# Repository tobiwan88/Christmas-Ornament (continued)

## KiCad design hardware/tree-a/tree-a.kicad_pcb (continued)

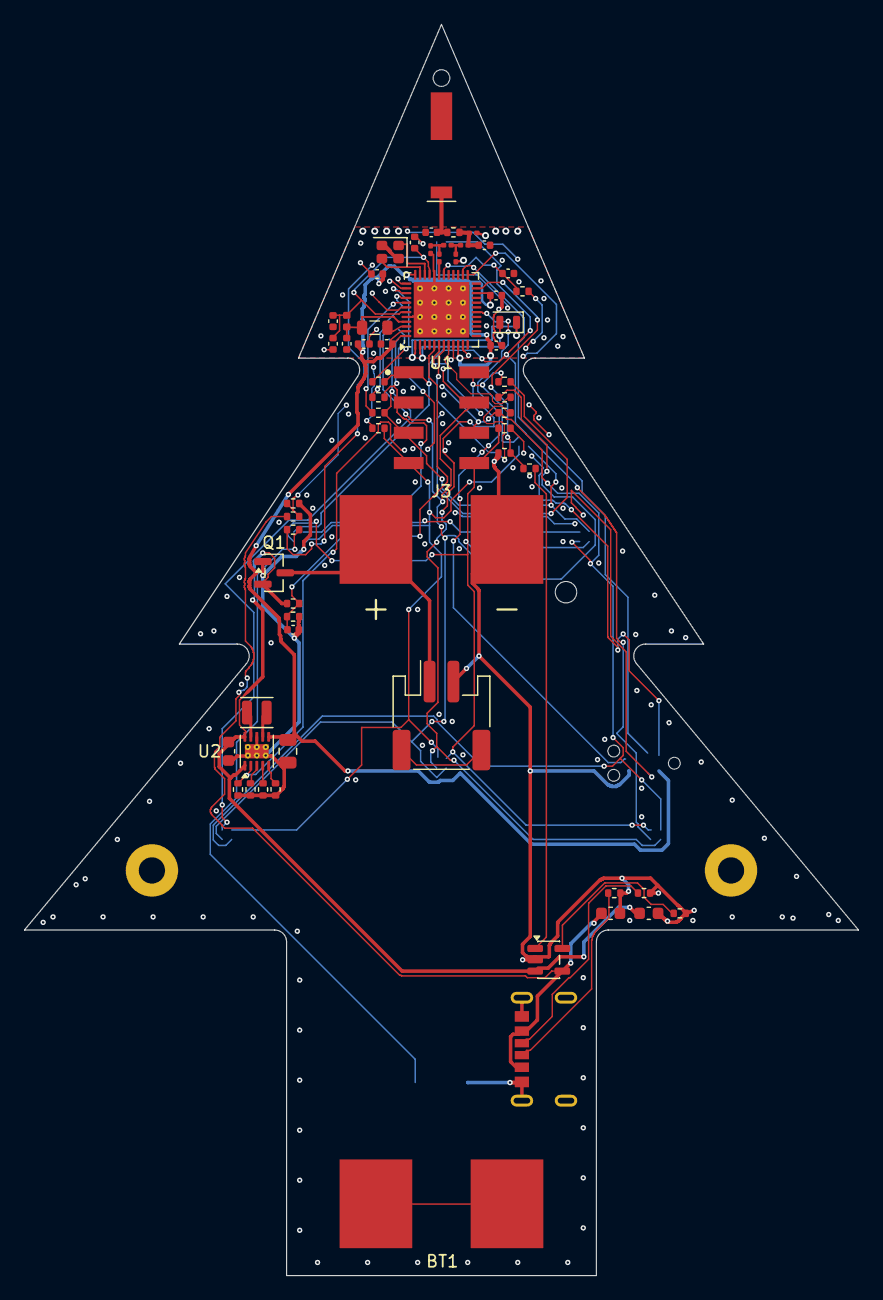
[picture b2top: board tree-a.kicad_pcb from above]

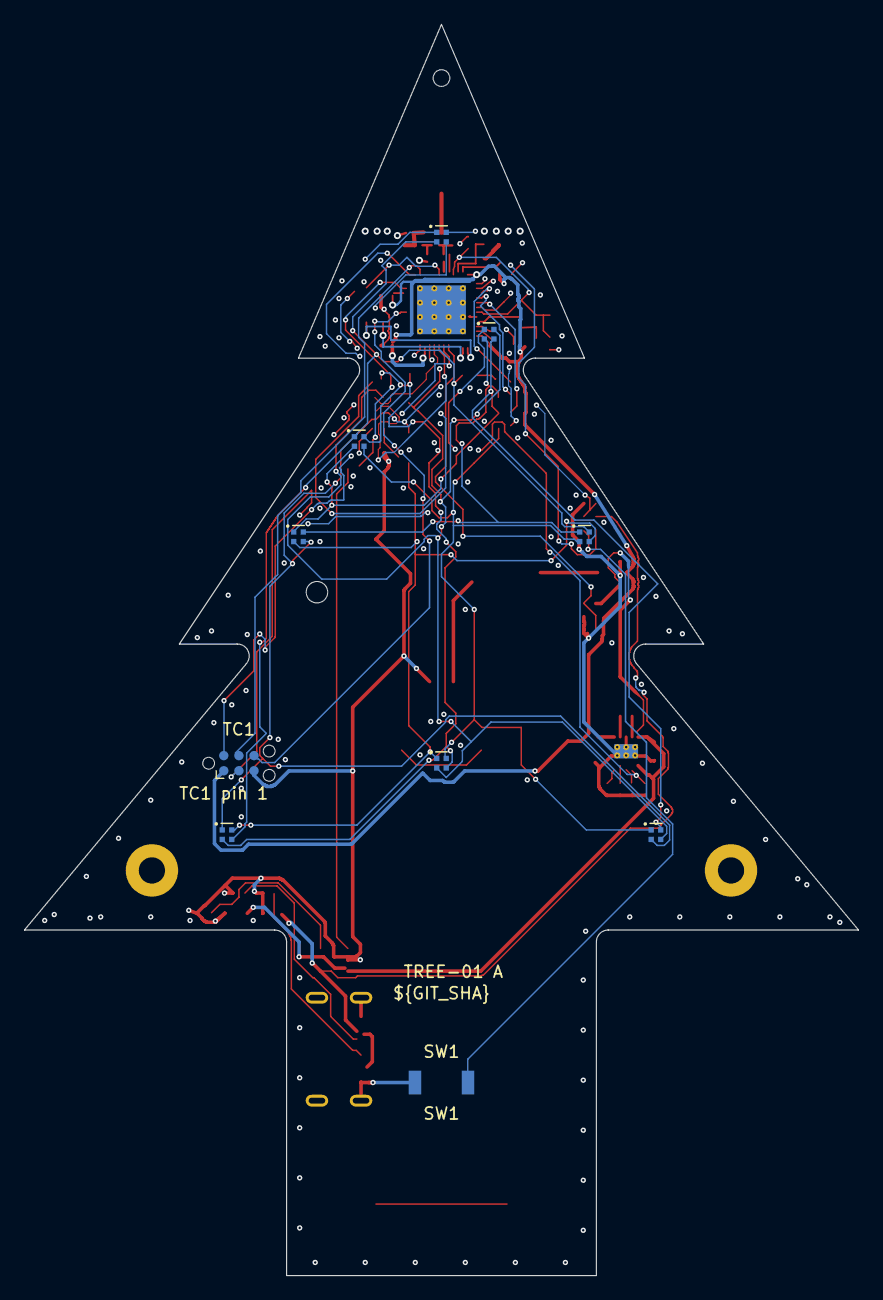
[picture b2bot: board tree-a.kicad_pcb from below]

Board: 4 copper layers, 70.0 x 105.0 mm, 75 parts (10 on the bottom side), 55 nets.

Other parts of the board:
H1: H_HANG; Hole_NPTH_1.4mm

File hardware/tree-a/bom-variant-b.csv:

Comment,Designator,Footprint,Quantity,LCSC Part #,Class,Status,Function / notes
2450AT42A100E (5x2mm),ANT1,ANT_Johanson_2450AT42A100E,1,C2917719,Extended,"datasheet card, stock 2026-11-23 (PARTS-REVIEW)","chip antenna (D12), feed pad 1 at the mark end (UNVERIFIED)"
2.2uF 6.3V X5R (0402),"C1,C2",C_0402_1005Metric,2,C12530,Basic,"datasheet card, stock 2026-11-23 (PARTS-REVIEW)",DECD (ref C1); DECA/DECRF (ref C2)
10uF 6.3V X5R (0402),C3,C_0402_1005Metric,1,C15525,Basic,"JLC listing only (jlcparts 2026-11-24, Basic, Samsung CL05A106MQ5NUNC): no card, DC-bias derating UNVERIFIED","VDD bulk at pins 47/48 (ref C3; 0402 for the gate-4 fan-out, alternate C19702 0603)"
100nF 50V X7R (0402),"C4,C7,C8,C10,C14",C_0402_1005Metric,5,C1525,Basic,"datasheet card, stock 2026-11-23 (PARTS-REVIEW)",VDD pin 36; VDD pin 10; VDD pin 22; VDD 47/48; VBAT_SENSE filter (DS-B2)
2.2nF 50V X7R (0402),C5,C_0402_1005Metric,1,C1531,Preferred,"datasheet card, stock 2026-11-23 (PARTS-REVIEW)",DECRF (ref C5)
1.5pF C0G +-0.05pF (0201),C6,C_0201_0603Metric,1,C435397,Extended,"datasheet card, stock 2026-11-23 (PARTS-REVIEW)","RF shunt, ground only via VSS_PA"
2.0pF C0G +-0.05pF (0201),C9,C_0201_0603Metric,1,C668326,Extended,"datasheet card, stock 2026-11-23 (PARTS-REVIEW)","RF shunt, GND via at the pad (KNOWN deviation: Nordic says bottom layer only)"
0.3pF C0G (0201),C11,C_0201_0603Metric,1,C161289,Extended,"datasheet card, stock 2026-11-23 (PARTS-REVIEW)",RF shunt at the 50 ohm node
10nF 50V X7R (0402),C12,C_0402_1005Metric,1,C15195,Basic,"datasheet card, stock 2026-11-23 (PARTS-REVIEW)",DECA/DECRF (ref C12)
3.9pF C0G (0402),C13,C_0402_1005Metric,1,C313081,Extended,"datasheet card, stock 2026-11-23 (PARTS-REVIEW)",nRESET filter (ref C13)
10uF 10V X5R (0603),C20,C_0603_1608Metric,1,C19702,Basic,"datasheet card, stock 2026-11-23 (PARTS-REVIEW)",TPS63900 Cin
22uF 25V X5R (0805),C21,C_0805_2012Metric,1,C45783,Basic,"datasheet card, stock 2026-11-23 (PARTS-REVIEW)",TPS63900 Cout
4.7uF 16V X5R (0603),"C30,C31",C_0603_1608Metric,2,C19666,Basic,"datasheet card, stock 2026-11-23 (PARTS-REVIEW)","charger Cin (variant B); charger Cout on VIN (variant B, D21)"
XL-1010RGB-YG (1010),"D9,D10,D11,D12,D13,D14,D15,D16",LED_XL-1010RGB-YG,8,C965834,Extended,"datasheet card, stock 2026-11-23 (PARTS-REVIEW)","RGB LED, outer face (B.Cu)"
120R/0.2A GZ1005D121TF (0402),FB1,L_0402_1005Metric,1,C38480,Extended,"datasheet card, stock 2026-11-23 (PARTS-REVIEW)",DECD to DECA/DECRF (ref FB1)
HC-TYPE-C-6P-01A (SMD),J1,USB_C_HCTL_HC-TYPE-C-6P-01A,1,C2894893,Extended,"datasheet card, stock 2026-11-23 (PARTS-REVIEW)",USB-C power input (variant B)
S2B-PH-SM4-TB (SMD PH),J2,JST_PH_S2B-PH-SM4-TB_1x02-1MP_P2.00mm_Horizontal,1,C295747,Extended,"datasheet card, stock 2026-11-23 (PARTS-REVIEW)",Li-ion pouch (variant B); pin 1 = cell + (UNVERIFIED)
HC-PM254-8.5H-2x4PS (SMD 2x4 2.54),J3,PinSocket_2x04_SMD_HC-PM254-8.5H,1,C22373945,Extended,"datasheet card, stock 2026-11-23 (PARTS-REVIEW)",female header to board B (D3)
4.7uH MPL2012S4R7MHT (0805),L1,L_0805_2012Metric,1,C63166,Extended,"datasheet card, stock 2026-11-23 (PARTS-REVIEW)",nRF DC/DC DCC-DECD (ref L1)
2.2uH SWPA252012S2R2MT (1008),L2,L_Sunlord_SWPA252012S,1,C23894,Extended,"datasheet card, stock 2026-11-23 (PARTS-REVIEW)","TPS63900 inductor, Isat 1.85 A"
2.7nH LQP03HQ2N7B02D (0201),L3,L_0201_0603Metric,1,C7216765,Extended,"datasheet card, stock 2026-11-23 (PARTS-REVIEW)",RF series (ref L2)
3.5nH LQP03HQ3N5B02D (0201),"L4,L5",L_0201_0603Metric,2,C3911055,Extended,"datasheet card, stock 2026-11-23 (PARTS-REVIEW)",RF series (ref L3); RF series (ref L4)
SI2301CDS-T1-GE3 (SOT-23),Q1,SOT-23,1,C10487,Basic,"datasheet card, stock 2026-11-23 (PARTS-REVIEW)","reverse-polarity P-FET, drain to cell + (D7)"
22R 1% (0402),"R1,R2,R3,R4,R5,R6,R7,R8",R_0402_1005Metric,8,C25092,Basic,"datasheet card, stock 2026-11-23 (PARTS-REVIEW)",line resistor LED_L1 (D13); line resistor LED_L2 (D13); line resistor LED_L3 (D13); line resistor LED_L4 (D13); line resistor LED_L5 (D13); line resistor LED_L6 (D13); line resistor LED_L7 (D13); line resistor LED_L8 (D13)
1k 1% (0402),"R9,R10",R_0402_1005Metric,2,C11702,Basic,"datasheet card, stock 2026-11-23 (PARTS-REVIEW)","nRESET series (ref R1); BTN_SW1 series, ESD current limit (D21, DS-C5)"
511R 1% 100ppm (0402),R20,R_0402_1005Metric,1,C25124,Extended,"datasheet card, stock 2026-11-23 (PARTS-REVIEW)",RCFG1: VO(2) 3.5 V (Table 7-2)
10.5k 1% 100ppm (0402),R21,R_0402_1005Metric,1,C25850,Extended,"datasheet card, stock 2026-11-23 (PARTS-REVIEW)",RCFG2: 100 mA input limit (Table 7-2)
13.3k 1% 100ppm (0402),R22,R_0402_1005Metric,1,C122547,Extended,"datasheet card, stock 2026-11-23 (PARTS-REVIEW)",RCFG3: VO(1) 3.0 V (Table 7-3)
1M 1% (0402),R23,R_0402_1005Metric,1,C26083,Basic,"datasheet card, stock 2026-11-23 (PARTS-REVIEW)",SEL pull-down (3.0 V at start)
5.1k 1% (0402),"R30,R31",R_0402_1005Metric,2,C25905,Basic,"datasheet card, stock 2026-11-23 (PARTS-REVIEW)",CC1 pull-down (variant B); CC2 pull-down (variant B)
10k 1% (0402),R32,R_0402_1005Metric,1,C25744,Basic,"datasheet card, stock 2026-11-23 (PARTS-REVIEW)",PROG 100 mA (variant B)
2.2M 1% 100ppm (0402),"R40,R41",R_0402_1005Metric,2,C5140754,Extended,"datasheet card, stock 2026-11-23 (PARTS-REVIEW)",battery divider top; battery divider bottom
100k 1% (0402),"R42,R44",R_0402_1005Metric,2,C25741,Basic,"datasheet card, stock 2026-11-23 (PARTS-REVIEW)",VBUS_DET divider top (tree_pin_divider.py); CHG_STAT divider top (tree_pin_divider.py)
120k 1% (0402),"R43,R45",R_0402_1005Metric,2,C25750,Preferred,"datasheet card, stock 2026-11-23 (PARTS-REVIEW)","VBUS_DET divider bottom; variant A: pull-down, reads low (D21, DS-B5); CHG_STAT divider bottom; variant A: pull-down, reads low (D21, DS-B5)"
0R (0402),R50,R_0402_1005Metric,1,C17168,Basic,"datasheet card, stock 2026-11-23 (PARTS-REVIEW)",pi series slot: bench-tune with a VNA
HX 3x4x2-2P-1.6N (SMD 4x3),SW1,SW_HX_3x4x2-2P-1.6N,1,C49234124,Extended,"datasheet card, stock 2026-11-23 (PARTS-REVIEW)","tact switch, outer face"
nRF54L10-QFAA-R7 (QFN-48 6x6),U1,QFN-48-1EP_6x6mm_P0.4mm_EP4.66x4.66mm_ThermalVias,1,C44800139,Extended,"datasheet card, stock 2026-11-23 (PARTS-REVIEW)","BLE SoC (D2); alternate nRF54L15-QFAA-R C42458750, same footprint"
TPS63900DSKR (WSON-10 2.5x2.5),U2,WSON-10-1EP_2.5x2.5mm_P0.5mm_EP1.2x2mm_ThermalVias,1,C1518762,Extended,"datasheet card, stock 2026-11-23 (PARTS-REVIEW)",buck-boost 3.0 / 3.5 V
MCP73831T-2ACI/OT (SOT-23-5),U3,SOT-23-5,1,C424093,Extended,"datasheet card, stock 2026-11-23 (PARTS-REVIEW)",Li-ion charger 100 mA (variant B)
32.768kHz ABS06-32.768KHZ-9-1-T (SMD2012-2P),X1,Crystal_SMD_2012-2Pin_2.0x1.2mm,1,C510776,Extended,"datasheet card, stock 2026-11-23 (PARTS-REVIEW)","LFXO, CL 9 pF, no external load caps"
32MHz XL7EL89CKI-111YLC-32M (SMD2016-4P),X2,Crystal_SMD_2016-4Pin_2.0x1.6mm,1,C2965582,Extended,"datasheet card, stock 2026-11-23 (PARTS-REVIEW)","HFXO, CL 8 pF, no external load caps"
tuning slot (0402),"C50,C51",C_0402_1005Metric,2,,n/a,DNP (no part),"pi shunt, antenna side of R50: bench-tune with a VNA; pi shunt, antenna pad side: bench-tune with a VNA"
TC2030-NL footprint (pads),TC1,Tag-Connect_TC2030-IDC-NL_2x03_P1.27mm_Vertical,1,,n/a,"DNP (DNL: footprint only, Tag-Connect cable)","SWD pads, outer face, no part (DNL)"

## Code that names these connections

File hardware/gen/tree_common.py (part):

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    {"net": "XL2", "gpio": "P1.01", "pin": 2, "kind": "xtal", "note": "LFXO"},
    {"net": "NC", "gpio": "P1.02", "pin": 3, "kind": "nc", "note": "NFC1, unused, leave open"},
    {"net": "NC", "gpio": "P1.03", "pin": 4, "kind": "nc", "note": "NFC2, unused, leave open"},
    {"net": "VBAT_SENSE", "gpio": "P1.04", "pin": 5, "kind": "ain", "v_source_max": 2.1,
     "note": "AIN0, battery divider mid-point (2.2M/2.2M after Q1, 100 nF filter: 4.2 V Li-ion -> 2.1 V); DC net, buffer between LFXO and LED lines"},
    {"net": "LED_L5_MCU", "gpio": "P1.05", "pin": 6, "kind": "led", "note": "via R5 to LED_L5"},
    {"net": "LED_L6_MCU", "gpio": "P1.06", "pin": 7, "kind": "led", "note": "via R6 to LED_L6"},
    {"net": "LED_L7_MCU", "gpio": "P1.07", "pin": 8, "kind": "led", "note": "via R7 to LED_L7"},
    {"net": "LED_L8_MCU", "gpio": "P1.08", "pin": 9, "kind": "led", "note": "via R8 to LED_L8 (P1.08 = EXTREF, not used)"},
    {"net": "TPS_SEL", "gpio": "P2.00", "pin": 11, "kind": "out",
     "note": "TPS63900 SEL: high = VO(2) lit, low = VO(1) 3.0 V; external pull-down (never float, 3.0 V at start)"},
    {"net": "SPARE_P2_01", "gpio": "P2.01", "pin": 12, "kind": "spare",
     "note": "spare; D13: TPS63900 EN tied to VIN, no GPIO (EN can see 4.2 V > VDD + 0.3 V)"},
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    {"net": "SPARE_P2_03", "gpio": "P2.03", "pin": 14, "kind": "spare", "note": "spare"},
    {"net": "SPARE_P2_04", "gpio": "P2.04", "pin": 15, "kind": "spare", "note": "spare"},
    {"net": "SPARE_P2_05", "gpio": "P2.05", "pin": 16, "kind": "spare", "note": "spare"},
    {"net": "SWO", "gpio": "P2.07", "pin": 18, "kind": "swo", "note": "optional to TC2030 pin 6 (TRACE pin)"},
    {"net": "CHG_STAT", "gpio": "P0.00", "pin": 23, "kind": "in", "v_source_max": V_DIVIDED_MAX,
     "conditioning": "D13: divider R44/R45 (tree_pin_divider.py); R45 alone pulls down in variant A (D21)",
     "note": "Li-ion variant; MCP73831 STAT low = charging, high = done, Hi-Z = shutdown/no battery"},
    {"net": "SPARE_P0_01", "gpio": "P0.01", "pin": 24, "kind": "spare", "note": "spare (wake capable)"},
    {"net": "SWDIO", "gpio": "SWDIO", "pin": 25, "kind": "swd", "note": "TC2030 pin 2"},
    {"net": "SWDCLK", "gpio": "SWDCLK", "pin": 26, "kind": "swd", "note": "TC2030 pin 4"},
    {"net": "SPARE_P0_02", "gpio": "P0.02", "pin": 27, "kind": "spare", "note": "spare, next to ANT: static use only"},
    {"net": "SPARE_P0_03", "gpio": "P0.03", "pin": 28, "kind": "spare", "note": "spare, next to ANT: static use only"},
    {"net": "SPARE_P0_04", "gpio": "P0.04", "pin": 29, "kind": "spare", "note": "spare, next to ANT: static use only"},
    {"net": "nRESET", "gpio": "nRESET", "pin": 30, "kind": "swd", "note": "TC2030 pin 3 via 1 k (Nordic reference R1/C13)"},
    {"net": "BTN_SW1", "gpio": "P1.09", "pin": 37, "kind": "in", "wake": True,
     "note": "SW1 to GND, internal pull-up; wake from System OFF (P1 SENSE)"},
    {"net": "VBUS_DET", "gpio": "P1.10", "pin": 38, "kind": "in", "wake": True, "v_source_max": V_DIVIDED_MAX,
     "conditioning": "D13: divider R42/R43 (tree_pin_divider.py); R43 alone pulls down in variant A (D21)",
     "note": "Li-ion variant; wakes on USB plug-in"},
    {"net": "LED_L1_MCU", "gpio": "P1.11", "pin": 39, "kind": "led", "note": "via R1 to LED_L1 (AIN4 unused)"},
    {"net": "LED_L2_MCU", "gpio": "P1.12", "pin": 40, "kind": "led", "note": "via R2 to LED_L2"},
    {"net": "LED_L3_MCU", "gpio": "P1.13", "pin": 41, "kind": "led", "note": "via R3 to LED_L3"},
    {"net": "LED_L4_MCU", "gpio": "P1.14", "pin": 42, "kind": "led", "note": "via R4 to LED_L4"},
]
LINE_GPIO = {e["net"][:-4]: e["gpio"] for e in PIN_PLAN if e["kind"] == "led"}     # {'LED_L1': 'P1.08', ...}
PIN_BY_NET = {e["net"]: e for e in PIN_PLAN if e["net"] != "NC"}

# ---------------------------------------------------------------- header J3 (A, female) / J4 (B, male), 2 x 4, 2.54 mm
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                      "line a+4 (mod 8, no die there): the ghost safety of R4.3 relies on it (red+red chains, 3.6 V, span "
                      "exactly those pairs).")
PIN_VOLTAGE_RULES = {
    "CHG_STAT": "MCP73831 STAT is push-pull to its VDD = VBUS (up to 5.25 V), above the nRF pin limit VDD + 0.3 V "
                "(3.3 V at VDD idle 3.0 V): divider R44/R45 gives <= 3.0 V at 5.25 V (tree_pin_divider.py, D13).",
    "VBUS_DET": "VBUS up to 5.25 V, above VDD + 0.3 V: divider R42/R43 gives <= 3.0 V at 5.25 V (tree_pin_divider.py, D13).",
}

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
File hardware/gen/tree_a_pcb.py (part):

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# U1 nRF54L QFN48, rotation 90: the RF side (pins 25-36, ANT = pin 31) faces UP to the antenna at the tip, so the
# matching network and the 50 ohm feed run straight up into the keep-out notch (Nordic's QFAA reference layout v0.8
# has the same network order ANT -> L3 / C6 (VSS_PA) -> L4 / C9 -> L5 / C11 next to the ANT pin; its feed then
# leaves sideways, ours turns to the tip). Power pins (43-48: DECA, DECD, DCC, VDD) face left, LFXO pins 1/2 are at
# the bottom-left corner, the quiet side (pins 13-24) faces right, HFXO pins 34/35 at the top-left.
# X >= 33.875 is forced: the KiCad ThermalVias footprint carries a 4.1 mm B.Cu pad and 16 through-vias (pad 49) that
# must clear LED D10's pads at (31, 26) on B.Cu (tree_geometry, fixed). X = 35.0 puts ANT pin 31 on the tip axis.
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    ("VBUS", "F.Cu", 0.127, [(18.55, 44.35), (20.283, 41.75), (20.733, 41.30), (22.04, 41.30)]),
    ("/charger/VBUS_DET", "F.Cu", 0.127, [(22.04, 40.20), (22.55, 40.75), (23.06, 41.30)]),
    ("/charger/VBUS_DET", "F.Cu", 0.127, [(22.55, 40.75), (22.55, 39.75), (22.95, 39.50)]),
    # U1 end: pins 37 (BTN_SW1) and 38 (VBUS_DET) shared one via spot in every run (the router took it for one of them).
    # VDD's via at C4.1 moves 0.4 mm left (29.75/21.75), BTN_SW1 goes down at 31.35/21.35 (0.53 mm from VDD's B.Cu run,
    # 0.5 mm hole-to-hole to VDD 36's via) with its In2 run north of the new VBUS_DET via 30.65/21.55 (0.19 mm to C4.1)
    ("/mcu/BTN_SW1", "F.Cu", 0.127, [(31.60, 21.75), (31.35, 21.50), (31.35, 21.35)]),
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    P.group = "rf"                           # --hand groups: rf (RF column, ANT_FEED, stitching row), fanout, xl, power
    # RF column from pins 31-33 straight up (perpendicular to the pin row), Nordic order ANT -> L3 / C6 -> L4 / C9 ->
    # L5 / C11 -> pi slot; 0201 parts at the IPC courtyard pitch 0.70
    P.put("L3", 34.82, 19.60, 90.0)          # pad 1 (ANT_PA) down at pin 31, pad 2 (RF_N1) up
    P.put("C6", 34.09, 18.90, 270.0)         # pad 2 (VSS_PA) down, fed from pin 32 by a track at x 34.31
    P.put("L4", 35.50, 18.53, 0.0)           # RF_N1 -> RF_N2
    P.put("C9", 36.20, 19.60, 270.0)         # pad 1 (RF_N2) up, pad 2 (GND) down to its own In1 via (decision 2)
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    T([(34.63, 17.45), (35.49, 17.45)], RF_W)                       # ANT_FEED: C51.1 - R50.2
    T([(35.00, 17.45), (35.00, 14.20)], RF_W)                       # ANT_FEED up the keep-out notch to ANT1 pad 1
    P.group = "fanout"
    # HFXO X2 and DECA C5 above pins 33-35. DECA pin 33 gets a dog-bone via (its only way out: XC1 and VSS_PA enclose
    # it) that also links it to DECA pin 43 on B.Cu; C5 (DECRF 2.2 nF) above the via
    P.put("X2", 30.70, 19.10, 180.0)         # pad 1 (XC1) top-right, pad 3 (XC2) bottom-left
    P.put("C5", 32.75, 18.30, 90.0)          # DECA pad 1 down at the via
    T([(34.00, 20.75), (34.00, 19.76), (33.52, 19.76), (33.30, 19.50)])             # DECA pin 33 to its via
    V(33.30, 19.50)
    T([(33.30, 19.50), (32.75, 19.00)])                             # into C5.1
    P.group = "close"        # gate 5 closing copper (coordinator): crystal + VDD links hand-drawn, the router does the rest
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    T([(32.05, 21.00), (31.95, 20.90), (30.08, 20.90)])
    T([(29.12, 20.95), (28.40, 21.60)])
    V(28.40, 21.60)                                                 # C4 GND via (In1)
    # nRESET pin 30: dog-bone via between L3 and C9; SWDCLK / SWDIO to vias at the top-right corner
    T([(35.20, 20.75), (35.20, 20.45), (35.50, 20.10)])
    V(35.50, 20.10)
    T([(36.80, 20.75), (36.80, 20.35), (38.90, 20.35)])
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    V(38.00, 21.00)
    P.put("C13", 40.60, 20.90, 0.0)          # nRESET filter: slow node, next to R9's route (known WARN)
    # right row: CHG_STAT 23 and SWO 18 to vias, VDD 22 into C8
    P.group = "close_esc"    # gate 5 closing copper: CHG_STAT pin 23 dog-bone (router left CHG_STAT open)
    T([(38.20, 22.15), (38.75, 22.15), (39.05, 21.85)])
    V(39.05, 21.85)
    P.group = "fanout"
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    for k in range(6):
        y = 21.75 + 0.4 * k
        vx, vy = 31.10 - 1.00 * k, 21.45 + 0.4 * k
        P.group = "close_esc" if k == 1 else "fanout"     # k 1 = VBUS_DET pin 38 (gate 5 closing copper)
        T([(31.80, y), (vx + 0.30, y), (vx, vy)])
        V(vx, vy)
    P.group = "fanout"
    # power cluster on the left row: DECA 43, GND 44 (to the exposed pad), DECD 45, DCC 46, VDD 47/48
    P.put("L1", 29.40, 25.45, 180.0)         # pad 1 (DCC) right at pin 46
    P.put("C10", 30.40, 26.82, 180.0)        # VDD 47/48, pad 1 right
    P.put("C3", 28.48, 26.82, 0.0)           # VDD 10 uF 0402 (B6), pad 1 (VDD) left, GND next to C10's GND
    P.put("FB1", 27.05, 24.90, 90.0)         # pad 2 (DECA) up on the DECA line, pad 1 (DECD) down to L1.2
    P.put("C1", 27.05, 26.80, 270.0)         # DECD, pad 1 up (below FB1.1) (B7: via spot at its GND pad)
    P.put("C12", 25.90, 24.90, 270.0)        # DECA 10 nF, pad 1 up at FB1.2
    P.put("C2", 25.90, 26.80, 270.0)         # DECA 2.2 uF
    T([(31.80, 24.15), (27.30, 24.15)])                             # DECA pin 43 to FB1.2 / C12
    T([(32.20, 24.55), (32.80, 24.55)], 0.20)                       # GND pin 44 into the exposed pad
    P.group = "close_decd"   # gate 5 closing copper: DECD pin 45 - L1.2 - FB1.1 - C1.1 (router left DECD open)
    T([(31.80, 24.95), (31.40, 24.95), (31.00, 24.55), (28.34, 24.55), (28.34, 24.95)])   # DECD 45 into L1.2
    P.group = "fanout"
    T([(31.80, 25.35), (30.60, 25.35)], 0.25)                       # DCC 46 into L1.1
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    V(36.55, 28.00)                                                 # VDD pin 10 to B.Cu (C7 / the VDD net)
    P.group = "fanout"
    T([(36.80, 27.15), (36.80, 27.45), (37.10, 27.75), (37.45, 27.95)])
    V(37.45, 27.95)                                                 # TPS_SEL pin 11 to B.Cu (U2 / R23 in the left wing)
    P.group = "close"
    T([(32.80, 27.15), (32.80, 27.60), (32.55, 27.95)])
    V(32.55, 27.95)                                                 # XL1 to B.Cu (X1 sits on the right side)
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    # carries only the LED lines L5-L8 (+ VDD / GND); the other left-strip parts moved out:
    #  - left wing column at x 22.55 between the edge and BT1 (one topology for the three inner nets: they leave the left
    #    row / bottom row on B.Cu between the via row and the exposed pad, run under J3 and under the holder, and cross
    #    no LED line): R43 / R42 (VBUS_DET, pin 38) and R10 (BTN_SW1, pin 37) above Q1; the battery divider R40 / R41 with
    #    C14 right below R41 under Q1 (R40's VIN pad next to Q1's source; VBAT_SENSE from pin 5 down J3's middle). C14 at
    #    the divider (review: at the divider or the pin; the pin side has no room, J3 courtyard 0.02 mm below U1)
    #  - first try (R43 at the right strip next to R42): VBUS_DET then crossed the bottom-row LED lines L1-L4: 23/28
    P.put("R43", 22.55, 40.20, 0.0)           # VBUS_DET pull-down (pin 38)
    T([(23.06, 40.20), (23.10, 39.35)])
    V(23.10, 39.35)                           # R43 GND via into In1 (escape proof: the pad was walled in by BTN / VBUS_DET)
    P.put("R42", 22.55, 41.30, 0.0)           # variant B VBUS_DET divider top (VBUS from J1 under the holder)
    P.put("R10", 22.55, 42.40, 0.0)           # BTN_SW1 series 1 k (pin 37)
    P.put("R40", 22.55, 48.60, 0.0)           # battery divider top, VIN pad 1 next to Q1's source
    P.put("R41", 22.55, 49.70, 0.0)           # battery divider bottom (VBAT_SENSE pad 1 left, GND right)
    P.put("C14", 22.55, 50.80, 0.0)           # VBAT_SENSE filter 100 nF right below R41 (pads stacked)
    P.put("R45", xr_r, yk(4.6), 180.0)        # CHG_STAT bottom (pin 23, right row)
    P.put("R9", 41.80, 22.40, 180.0)         # nRESET series to TC1 pad 3: next to C13 at the top-right corner (gate 4)
    P.put("R44", xr_r + 2.1, yk(5.6), 180.0)
    # ---- 4. power: Q1 at BT1 pad 1 (BAT), TPS63900 stage in the left wing ------------------------------------------------
    b1 = P.pad("BT1", "1")
    P.put("Q1", b1[0] - 3.05 - 5.5, b1[1] + 2.8, 0.0)   # drain (pin 3) faces the BAT pad
    P.put("U2", *U2_XY, 90.0)                           # pins 6-10 on top (VOUT right, VIN left) as TI Figure 10-1
    ux, uy = U2_XY
    P.put("L2", ux, uy - 1.93 - 1.29 - 0.03, 0.0)       # LX1 left, LX2 right, above the IC
    P.put("C20", ux - 1.54 - 0.78 - 0.05, uy, 270.0)    # Cin, pad 1 (VIN) up at pin 10
    P.put("C21", ux + 1.54 + 1.02 + 0.05, uy, 270.0)    # Cout, pad 1 (VDD) up at pin 6
    yb = uy + 1.93 + 0.97 + 0.30                         # 0.27 below the courtyard touch: clear of U2's pin-1 silk mark
    for k, ref in enumerate(("R23", "R20", "R21", "R22")):   # SEL pull-down, CFG1, CFG2, CFG3 under pins 2-5
        P.put(ref, ux - 1.575 + 1.05 * k, yb, 270.0)
    P.group = "power"
    power_stage(P)
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

def _vdd_links(P, T, V):
    # VDD: pin 10 via (36.55, 28.00) -> B.Cu below the TPS_SEL via -> via at C7.1 -> C7.1 (F.Cu)
    c7 = P.pad("C7", "1")
    vx, vy = c7[0], round(c7[1] + 0.85, 3)
    T([(36.55, 28.00), (36.55, 28.60), (vx - 0.30, 28.60), (vx, 28.30), (vx, vy)], 0.3, "B.Cu")
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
